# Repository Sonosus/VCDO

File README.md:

# VCDO
This is a voltage controlled digital wavetable oscillator based around the Electric Druid VCDO1(PIC16F1847) microcontroller chip.

[![CC BY-SA 4.0][cc-by-sa-shield]][cc-by-sa]

This work is licensed under a
[Creative Commons Attribution-ShareAlike 4.0 International License][cc-by-sa].

[![CC BY-SA 4.0][cc-by-sa-image]][cc-by-sa]

[cc-by-sa]: http://creativecommons.org/licenses/by-sa/4.0/
[cc-by-sa-image]: https://licensebuttons.net/l/by-sa/4.0/88x31.png
[cc-by-sa-shield]: https://img.shields.io/badge/License-CC%20BY--SA%204.0-lightgrey.svg

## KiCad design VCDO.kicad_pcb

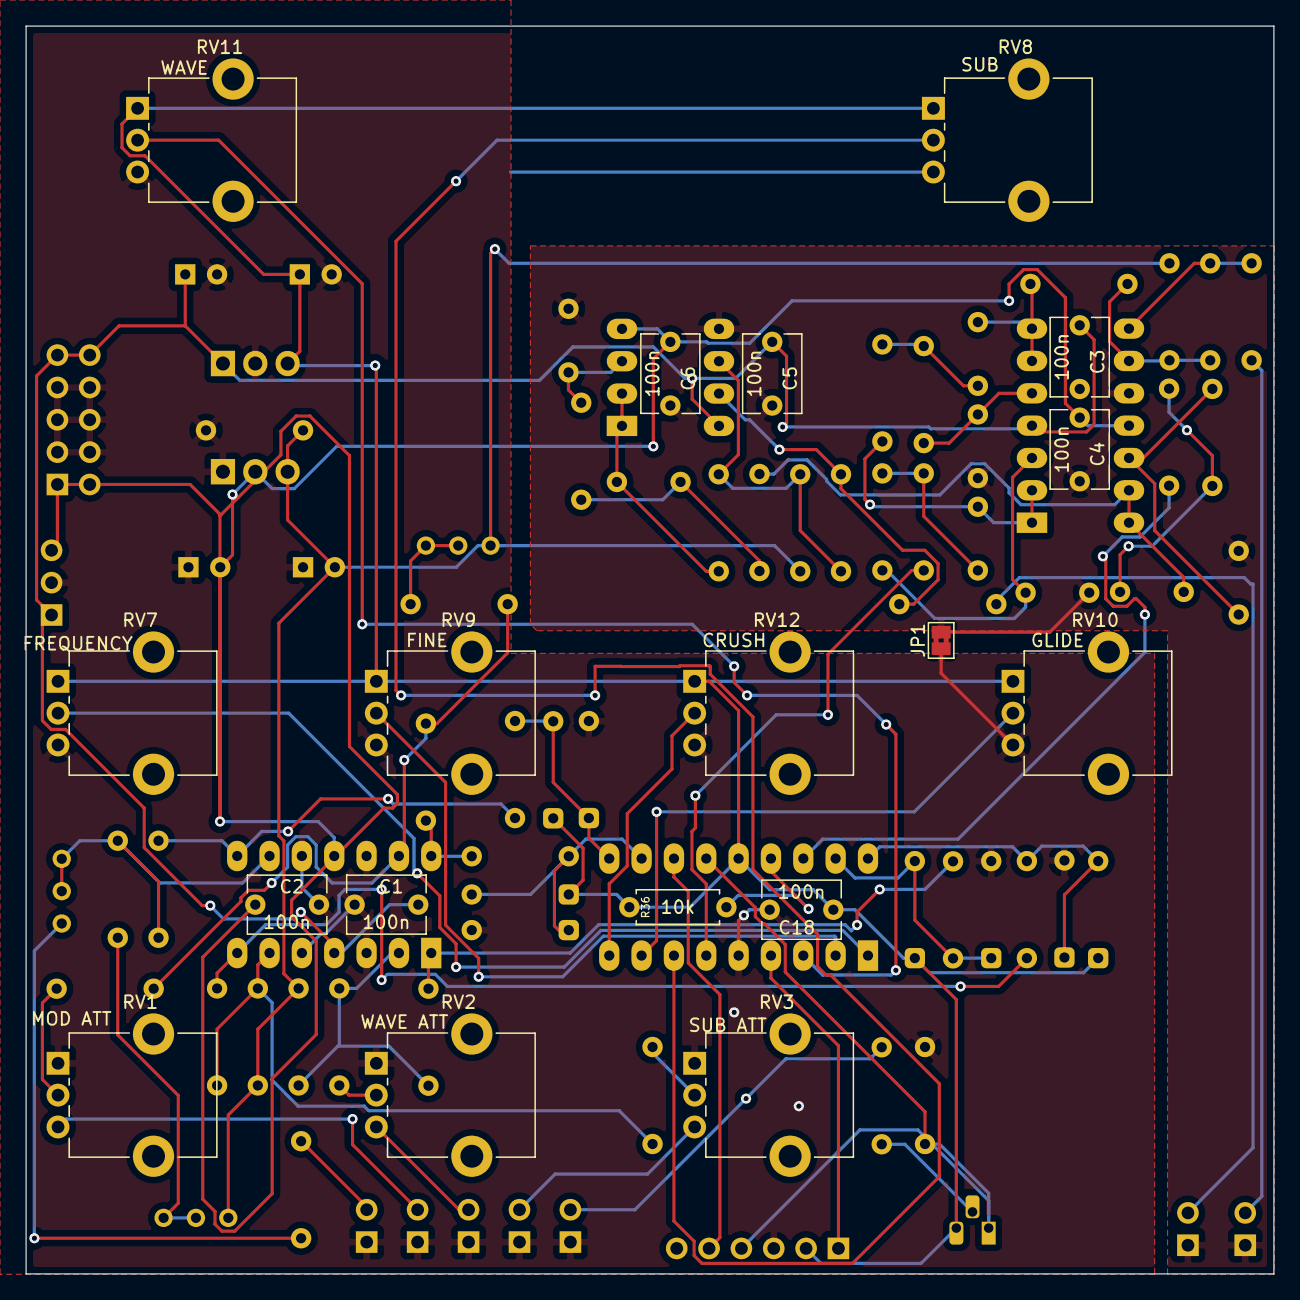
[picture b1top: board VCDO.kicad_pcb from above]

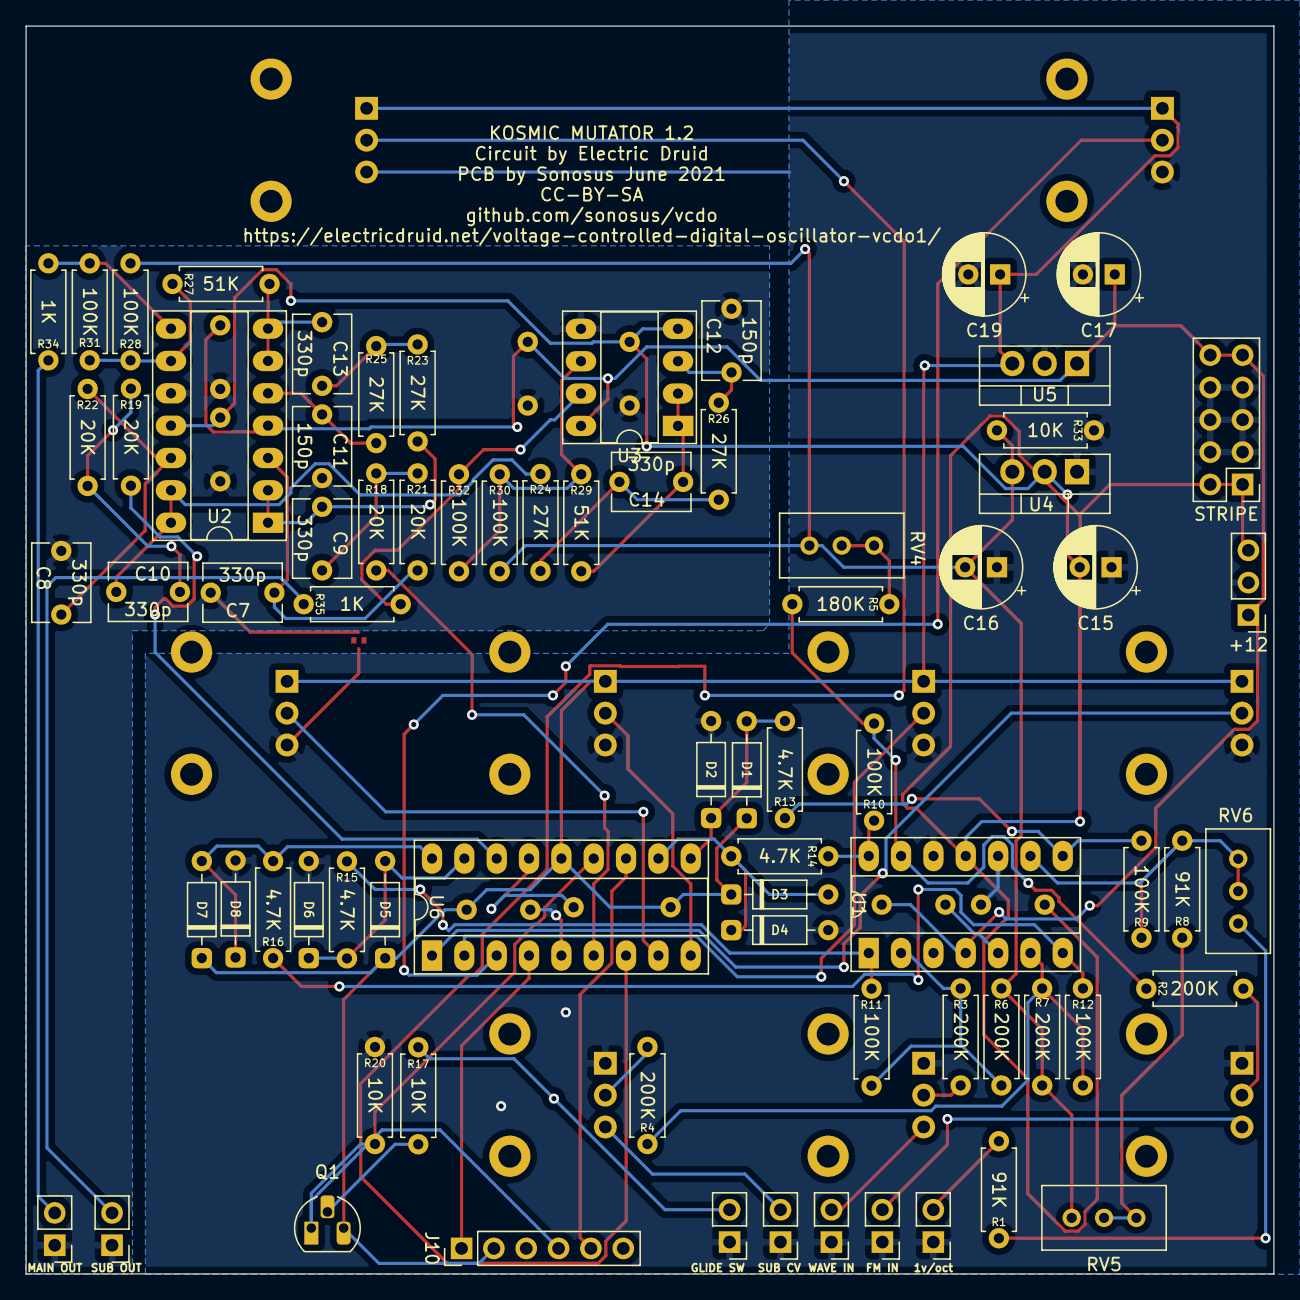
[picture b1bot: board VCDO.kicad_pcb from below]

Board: 2 copper layers, 98.0 x 98.0 mm, 93 parts (75 on the bottom side), 60 nets.

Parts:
1v/oct: NOTE CV; PinHeader_1x02_P2.54mm_Vertical
+12: TEST HEADER; PinHeader_1x03_P2.54mm_Vertical
C1, C2, C3, C4, C5, C6, C18: 100n; Capacitor_NonPolarized
C7, C8, C9, C10, C13, C14: 330p; Capacitor_NonPolarized
C11, C12: 150p; Capacitor_NonPolarized
C15, C16, C17, C19: 100uF; Capacitor_Polarized
D1, D2, D3, D4, D5, D6, D7, D8: D_Schottky; Diode_DO-35
FM IN: MOD CV; PinHeader_1x02_P2.54mm_Vertical
GLIDE SW: GLIDE TOGGLE; PinHeader_1x02_P2.54mm_Vertical
J10: PROGRAMMING HEADER; PinHeader_1x06_P2.54mm_Vertical
JP1: Jumper_2_Bridged; SolderJumper-2_P1.3mm_Bridged2Bar_Pad1.0x1.5mm
MAIN OUT: MAIN OUT; PinHeader_1x02_P2.54mm_Vertical
Q1: 2N3904; Transistor_TO-92
R1, R8: 91K; Resistor
R2, R3, R4, R6, R7: 200K; Resistor
R5: 180K; Resistor
R9, R10, R11, R12, R28, R30, R31, R32: 100K; Resistor
R13, R14, R15, R16: 4.7K; Resistor
R17, R20: 10K; Resistor
R18, R19, R21, R22: 20K; Resistor
R23, R24, R25, R26: 27K; Resistor
R27, R29: 51K; Resistor
R33: 10K OPTIONAL; Resistor
R34, R35: 1K; Resistor
R36: 10k; Resistor
RV1: MOD ATT; Potentiometer_Alpha_RD901F-40-00D_centred
RV2: WAVE ATT; Potentiometer_Alpha_RD901F-40-00D_centred
RV3: SUB ATT; Potentiometer_Alpha_RD901F-40-00D_centred
RV4: 47K; Potentiometer_Bourns_3296W_Vertical
RV5: 20K offset; Potentiometer_Bourns_3296W_Vertical
RV6: 20K 1v/oct; Potentiometer_Bourns_3296W_Vertical
RV7: FREQUENCY; Potentiometer_Alpha_RD901F-40-00D_centred
RV8: SUB; Potentiometer_Alpha_RD901F-40-00D_centred
RV9: FINE; Potentiometer_Alpha_RD901F-40-00D_centred
RV10: GLIDE; Potentiometer_Alpha_RD901F-40-00D_centred
RV11: WAVE; Potentiometer_Alpha_RD901F-40-00D_centred
RV12: CRUSH; Potentiometer_Alpha_RD901F-40-00D_centred
STRIPE: SYNTH POWER; PinHeader_2x05_P2.54mm_Vertical
SUB CV: SUB CV; PinHeader_1x02_P2.54mm_Vertical
SUB OUT: SUB OUT; PinHeader_1x02_P2.54mm_Vertical
U1, U2: TL074; DIP-14_Socket
U3: TL072; DIP-8_Socket
U4: L7905; TO-220-3_Vertical
U5: L7805; TO-220-3_Vertical
U6: Druid VCDO; DIP-18_W7.62mm_Socket_LongPads
WAVE IN: WAVE CV; PinHeader_1x02_P2.54mm_Vertical

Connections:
+5V: C18.1, C19.1, D1.1, D3.1, D5.1, D7.1, J10.2, Q1.3, R36.1, RV7.1, RV8.1, RV9.1, RV10.1, RV11.1, RV12.1, U5.3, U6.14
+12V: +12.1, C1.2, C3.1, C5.1, C17.1, STRIPE.9, STRIPE.10, U1.4, U2.4, U3.8, U5.1
-5V: C16.2, R6.1, R7.1, R28.2, R30.2, R33.2, RV4.1, RV5.1, U4.3
-12V: +12.3, C2.1, C4.1, C6.1, C15.2, STRIPE.1, STRIPE.2, U1.11, U2.11, U3.4, U4.2
CRUSHPOT: RV12.2, U6.9
FINEPOT: RV9.2, U6.2
FREQPOT: RV7.2, U6.1
GLIDEPOT: RV10.2, U6.8
GLIDE_IN: GLIDE SW.2, R17.2
GLIDE_PIN: J10.4, Q1.1, R20.2, U6.13
GND: 1v/oct.1, +12.2, C1.1, C2.2, C15.1, C16.1, C17.2, C18.2, C19.2, D2.2, D4.2, D6.2, D8.2, FM IN.1, GLIDE SW.1, J10.3, JP1.1, R20.1, R33.1, RV1.1, RV2.1, RV3.1, RV7.3, RV8.3, RV9.3, RV10.3, RV11.3, RV12.3, STRIPE.3, STRIPE.4, STRIPE.5, STRIPE.6, STRIPE.7, STRIPE.8, SUB CV.1, U1.3, U1.5, U1.10, U1.12, U4.1, U5.2, U6.5, WAVE IN.1
GNDA: C3.2, C4.2, C5.2, C6.2, C7.2, C8.2, C11.2, C12.2, JP1.2, MAIN OUT.1, SUB OUT.1, U2.10, U3.5
MAINOUT: MAIN OUT.2, R34.1
MAIN_PIN: R18.2, U6.6
MCLR: J10.1, U6.4
MOD_CV: D3.2, D4.1, R14.2, U6.11
MOD_IN: FM IN.2, RV1.3
NOTE_CV: D1.2, D2.1, R13.2, U6.10
NOTE_IN: 1v/oct.2, R1.2
unnamed: C7.1, R21.1, U2.3
unnamed: C8.1, R22.1, U2.12
unnamed: C9.1, R23.2, U2.1, U2.2
unnamed: C9.2, R18.1, R21.2
unnamed: C10.1, R24.2, U2.13, U2.14
unnamed: C10.2, R19.1, R22.2
unnamed: C11.1, R25.1, U2.5
unnamed: C12.1, R26.1, U3.3
unnamed: C13.1, R27.2, U2.6, U2.7
unnamed: C13.2, R23.1, R25.2
unnamed: C14.1, R29.2, U3.1, U3.2
unnamed: C14.2, R24.1, R26.2
unnamed: Q1.2, R17.1
unnamed: R1.1, RV6.1
unnamed: R2.2, RV1.2
unnamed: R3.2, RV2.2
unnamed: R4.2, RV3.2
unnamed: R5.1, RV4.2, RV4.3
unnamed: R8.1, RV5.2, RV5.3
unnamed: R8.2, R9.2, RV6.2, RV6.3, U1.9
unnamed: R10.1, R14.1, U1.14
unnamed: R2.1, R5.2, R10.2, U1.13
unnamed: R11.1, R15.1, U1.1
unnamed: R3.1, R6.2, R11.2, U1.2
unnamed: R12.1, R16.1, U1.7
unnamed: R4.1, R7.2, R12.2, U1.6
unnamed: R9.1, R13.1, U1.8
unnamed: R27.1, R28.1, R31.2, U2.9
unnamed: R29.1, R30.1, R32.2, U3.6
unnamed: R31.1, R34.2, U2.8
unnamed: R32.1, R35.2, U3.7
unnamed: R36.2, U6.15
PROGCLK: J10.5, U6.12
SUBOUT: R35.1, SUB OUT.2
SUBPOT: RV8.2, U6.7
SUB_CV: D7.2, D8.1, R16.2, U6.18
SUB_IN: RV3.3, SUB CV.2
SUB_PIN: R19.2, U6.16
WAVEPOT: RV11.2, U6.3
WAVE_CV: D5.2, D6.1, R15.2, U6.17
WAVE_IN: RV2.3, WAVE IN.2

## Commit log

2021-05-23 Upload PCB files for daughterboard
2021-05-24 [ImgBot] Optimize images
    /out.svg -- 737.67kb -> 576.64kb (21.83%)
2021-06-05 Revert "[ImgBot] Optimize images"
    This reverts commit a935d3664e1a0997f207a3b0d78a44b66787a09a.
2021-06-05 Revert "Merge pull request #1 from Sonosus/imgbot"
    This reverts commit d05c083b787ac3f04af39e1e5e7584b2d71e6cf9.
2021-06-05 Revert "[ImgBot] Optimize images"
    This reverts commit 08409d610a5a578c9b311537960838eacb380ea4.
2021-06-06 add panel
2021-06-06 remove daughter conn, add att pots
2021-06-06 power
2021-06-06 regulators
2021-06-06 no more conn, add pots
2021-06-08 reannotate
2021-06-08 pwr flags
2021-06-08 no more resistors or caps on pots
2021-06-08 fooootprints
2021-06-08 initial pcb
2021-06-11 'fresh files
2021-06-12 complete panel
2021-06-12 export svg to individual layers
2021-06-12 whoops
2021-06-12 start panel and pcb - edge cuts
2021-06-12 move pot
2021-06-12 ughhh i missed 3 pots :-(
2021-06-12 ill do more tomorrow...
2021-06-20 symlibtable
2021-06-21 Revert "convert to nightly.... sorry kicad v5!"
    This reverts commit 3fae462715a3255d148ad6eec04f1526b4d9dbf0.
2021-06-21 add caps again, back to v5
2021-06-22 onshape link
2021-06-22 import dxf and add 2 pots
2021-06-22 save
2021-06-25 position pots to panel
2021-06-25 panel
2021-06-25 shufflio
2021-06-25 edge cuts
2021-06-25 oops
2021-06-26 add 3d models, sort orientations
2021-06-26 saveagain
2021-06-26 maybe?
2021-06-26 sayve
2021-06-26 nearly there
2021-06-26 almost
2021-06-29 tracks!
2021-06-30 del tracks
2021-06-30 analogue tracks
2021-06-30 woot woot
2021-06-30 silk
2021-06-30 ibom
2021-06-30 plot schem
2021-06-30 gerbers
2021-06-30 smaller board
2021-06-30 zip again, update bom
